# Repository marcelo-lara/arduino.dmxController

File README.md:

# DragonBox DMX Controller

---
## Background context
Inside a room with 'hidden' light effects, there is a box with celtic dragons inscriptions. When you open it, the 'dungeon scene' is played and you can control lighting and effects with the box.

## Technical reference
- One server, many addressable slaves.
- RF transport with nrf24l01. RF24 Library https://github.com/nRF24/RF24
- DMX protocol forked from https://github.com/mathertel/DMXSerial | Copyright (c) 2005-2015 by Matthias Hertel, http://www.mathertel.de

---
### DMX Box controller (dmxServer)
- AtMega328P Controller + nrf24l01P
- Analog joystic
- Buttons to control scenes/chases/blackout

### DMX slave
- AtMega328P Controller + nrf24l01P on shielded box
- Led indicators for Pwr / Status / Dmx tx
- Lights power on/off with SSR controlled by 74HC595 shiftout register
- DMX cascaded network

### dragon DMX library
Common library

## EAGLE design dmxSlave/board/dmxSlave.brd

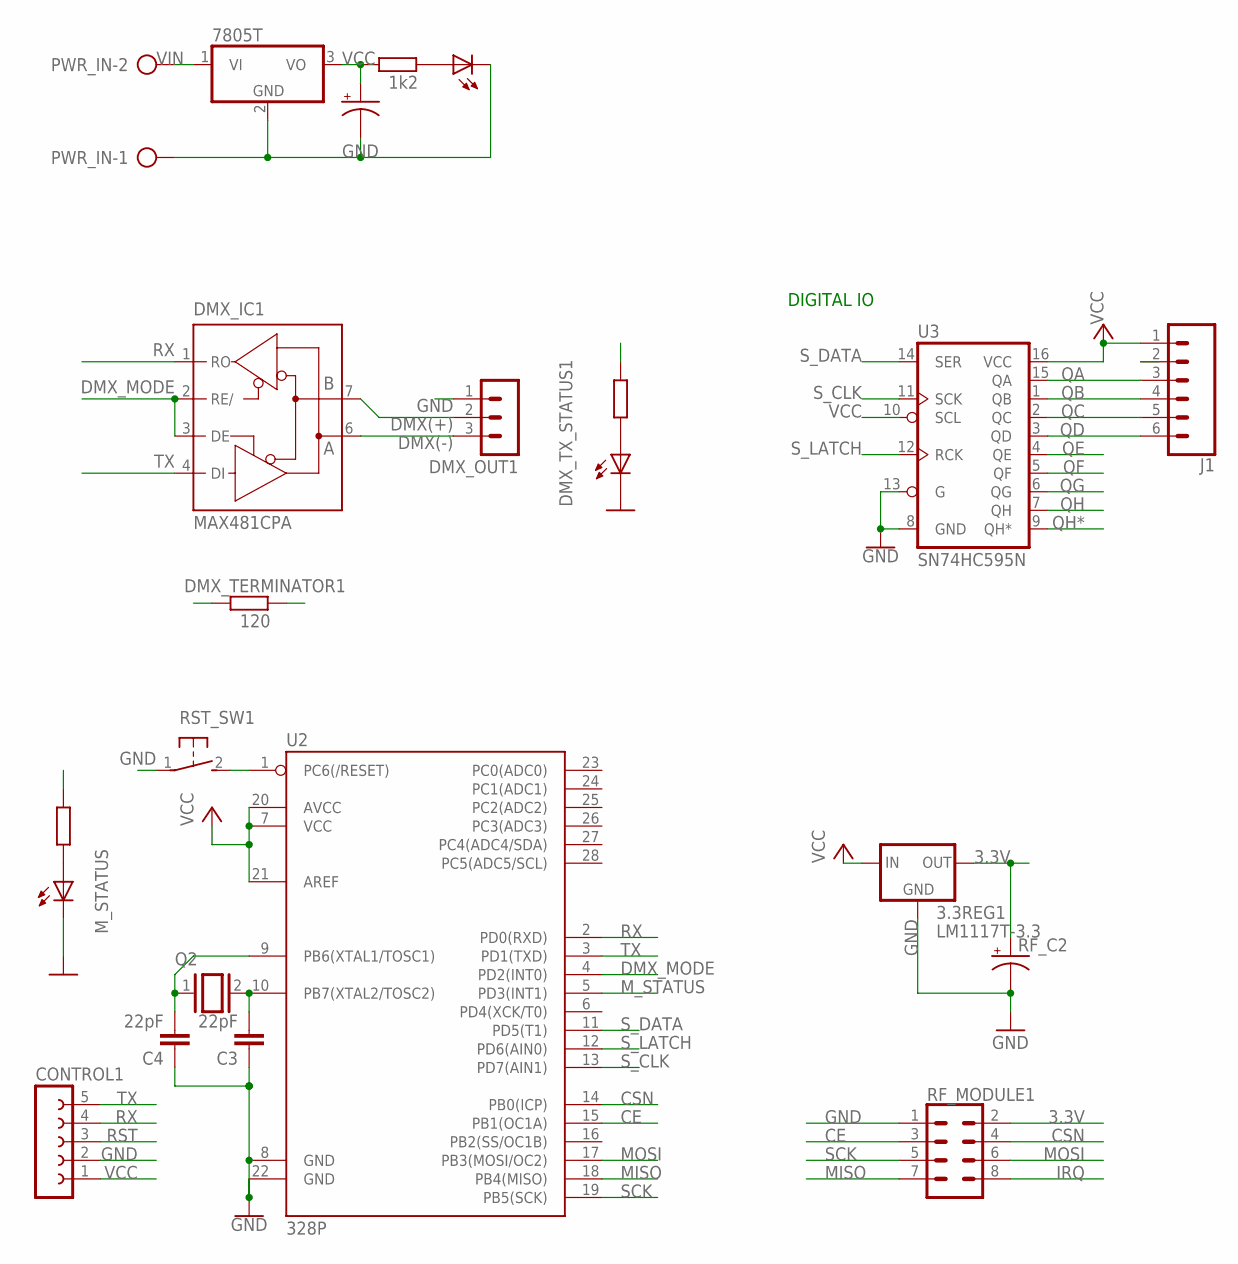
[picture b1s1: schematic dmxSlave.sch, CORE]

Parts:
3.3REG1: LM1117T-3.3; TO220
C3, C4: 22pF; C050-030X075
CONTROL1: FE05-1
DMX_IC1: MAX481CPA; DIL08
DMX_OUT1: MA03-1
DMX_R1: 0204/5
DMX_TERMINATOR1: 120; 0204/5
DMX_TX_STATUS1: LED3MM
J1: CONN_06NO_SILK_FEMALE_PTH; 1X06_NO_SILK
M_STATUS: LED3MM
M_STATUS_R1: 0207/10
PWR_C1: CPOL-USE5-10.5; E5-10,5
PWR_IC1: 7805T; TO220H
PWR_IN: AK500/2-H
PWR_L1: LED3MM
PWR_R1: 1k2; 0204/5
Q2: 16MHz; QS
RF_C2: CPOL-USE5-10.5; E5-10,5
RF_MODULE1: CONN_04X2; 2X4
RST_SW1: DTS-3
U2: 328P; DIP28
U3: SN74HC595N; DIP16

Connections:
3.3V: 3.3REG1.2 (OUT), RF_C2.+, RF_MODULE1.2
CE: RF_MODULE1.3, U2.15 (PB1(OC1A))
CSN: RF_MODULE1.4, U2.14 (PB0(ICP))
DMX(+): DMX_IC1.7 (B), DMX_OUT1.2, DMX_R1.2, DMX_TERMINATOR1.2
DMX(-): DMX_IC1.6 (A), DMX_OUT1.3, DMX_TERMINATOR1.1
DMX_MODE: DMX_IC1.2 (RE/), DMX_IC1.3 (DE), U2.4 (PD2(INT0))
DMX_TX_STATUS_LEF1: M_STATUS.A, M_STATUS_R1.1
DMX_TX_STATUS_LEF2: DMX_R1.1, DMX_TX_STATUS1.A
GND: 3.3REG1.1 (GND), C3.1, C4.1, CONTROL1.2, DMX_IC1.5 (GND), DMX_OUT1.1, DMX_TX_STATUS1.K (C), J1.2, M_STATUS.K (C), PWR_C1.-, PWR_IC1.2 (GND), PWR_IN.1, PWR_L1.K (C), RF_C2.-, RF_MODULE1.1, RST_SW1.1, U2.8 (GND), U2.22 (GND), U3.8 (GND), U3.13 (G)
IRQ: RF_MODULE1.8
MISO: RF_MODULE1.7, U2.18 (PB4(MISO))
MOSI: RF_MODULE1.6, U2.17 (PB3(MOSI/OC2))
M_STATUS: M_STATUS_R1.2, U2.5 (PD3(INT1))
unnamed: PWR_L1.A, PWR_R1.2
QA: J1.3, U3.15 (QA)
QB: J1.4, U3.1 (QB)
QC: J1.5, U3.2 (QC)
QD: J1.6, U3.3 (QD)
QE: U3.4 (QE)
QF: U3.5 (QF)
QG: U3.6 (QG)
QH: U3.7 (QH)
QH*: U3.9 (QH*)
RST: CONTROL1.3, RST_SW1.2, U2.1 (PC6(/RESET))
RX: CONTROL1.4, DMX_IC1.1 (RO), U2.2 (PD0(RXD))
SCK: RF_MODULE1.5, U2.19 (PB5(SCK))
S_CLK: U2.13 (PD7(AIN1)), U3.11 (SCK)
S_DATA: U2.11 (PD5(T1)), U3.14 (SER)
S_LATCH: U2.12 (PD6(AIN0)), U3.12 (RCK)
TX: CONTROL1.5, DMX_IC1.4 (DI), U2.3 (PD1(TXD))
VCC: 3.3REG1.3 (IN), CONTROL1.1, DMX_IC1.8 (VCC), J1.1, PWR_C1.+, PWR_IC1.3 (VO), PWR_R1.1, U2.7 (VCC), U2.20 (AVCC), U2.21 (AREF), U3.10 (SCL), U3.16 (VCC)
VIN: PWR_IC1.1 (VI), PWR_IN.2
X3: C4.2, Q2.1, U2.9 (PB6(XTAL1/TOSC1))
X4: C3.2, Q2.2, U2.10 (PB7(XTAL2/TOSC2))

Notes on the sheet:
DIGITAL IO

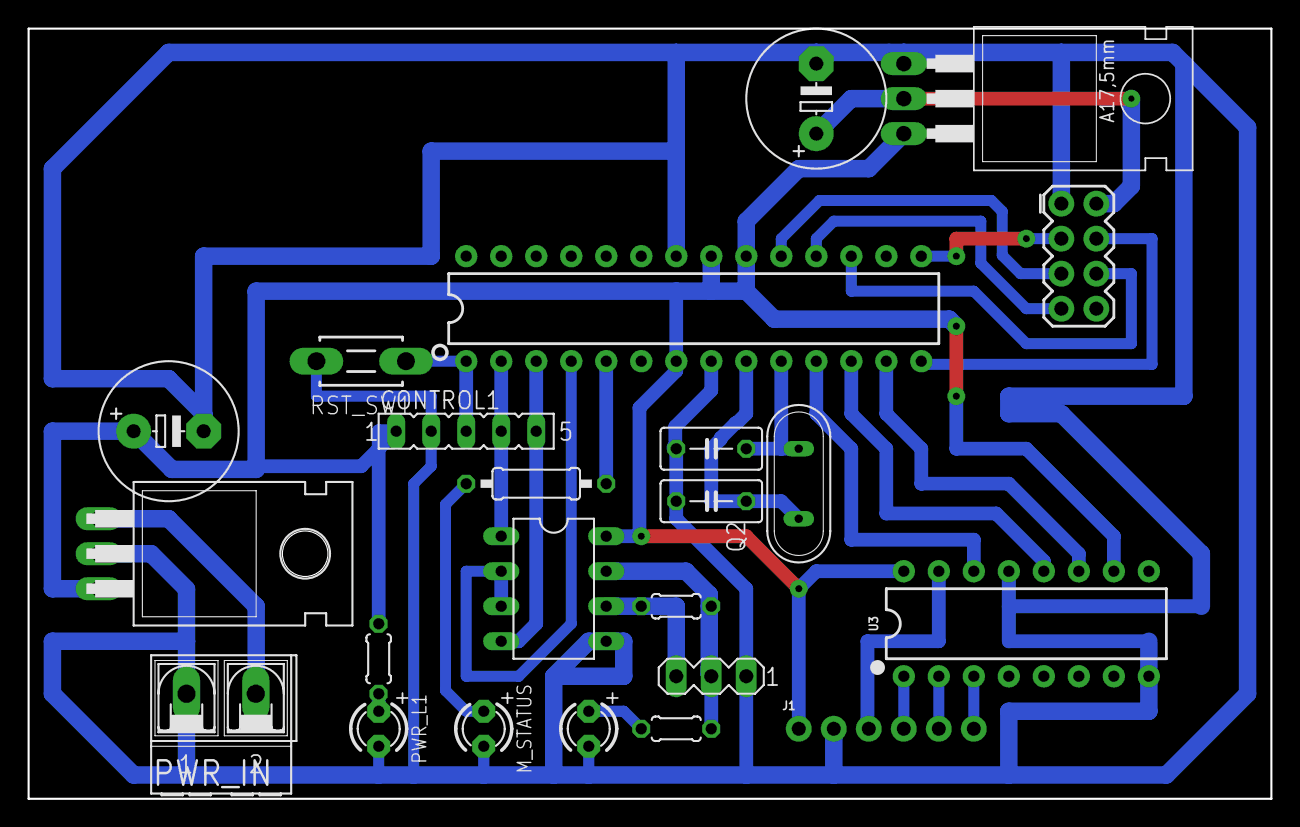
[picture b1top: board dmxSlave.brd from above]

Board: 2 copper layers, 90.2 x 55.9 mm, 23 parts (0 on the bottom side), 28 nets.

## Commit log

2019-05-11 update description
2019-05-11 vscode settings
2019-05-11 dmxSlave boards+sketch
2019-05-11 ignore vscode folder
2019-05-11 init dmx library
2019-05-18 rf config in external file
2019-05-26 config update
2019-05-27 MovingHead Fixture definitions
2019-05-27 WIP: joystick move fxHead
2019-05-29 boxController: joystick bugfixes
2019-05-29 RfDmxPacket definition
2019-06-05 master: rf handling

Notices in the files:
parts and their libraries:
SparkFun-IC-Microcontroller: Licensing: Creative Commons ShareAlike 4.0 International - https://creativecommons.org/licenses/by-sa/4.0
